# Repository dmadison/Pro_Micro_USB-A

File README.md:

Pro Micro w/ USB-A
=========

The Pro Micro is a micro controller with an ATMega32U4 IC on board.
The USB transceiver is inside the 32U4, adding USB connectivity on-board without external USB interfaces. 
This comes in both a 3.3V and 5V version. 

This repository was forked from [the original SparkFun Pro Micro repository](https://github.com/sparkfun/Pro_Micro). The board has been modified to use [a USB-A](https://en.wikipedia.org/wiki/USB_hardware#Connectors) connector.

For more information, see [the blog post on PartsNotIncluded.com](https://www.partsnotincluded.com/sparkfun-pro-micro-with-usb-a/).

Repository Contents
-------------------
* **/Documentation** - Data sheets (.pdf and .svg)
* **/Firmware** - Arduino example code used in the hookup guide
* **/Hardware** - All Eagle design files (.brd, .sch, .STL)
* **/Production** - Test bed files and production panel files

Documentation
--------------
* **[Hookup Guide](https://learn.sparkfun.com/tutorials/pro-micro--fio-v3-hookup-guide)** - Basic hookup guide for the Pro Micro.
* **[SparkFun Arduino Board Addon](https://github.com/sparkfun/Arduino_Boards/)** - Arduino board addon for Pro Micro.
* **[SparkFun Graphical Datasheets](https://github.com/sparkfun/Graphical_Datasheets)** - Graphical datasheets for various SparkFun products.
* **[USB-A Build Log](https://www.partsnotincluded.com/sparkfun-pro-micro-with-usb-a/)** - Build log for the USB-A version on PartsNotIncluded.com

Product Versions
----------------
* [DEV-12587](https://www.sparkfun.com/products/12587)- 3.3V/8MHz version
* [DEV-12640](https://www.sparkfun.com/products/12640)- 5V/16MHz version

License Information
-------------------
This product is _**open source**_! 

Please review the LICENSE.md file for license information. 

If you have any questions or concerns on licensing, please contact techsupport@sparkfun.com.

Distributed as-is; no warranty is given.

- Your friends at SparkFun.

_<COLLABORATION CREDIT>_

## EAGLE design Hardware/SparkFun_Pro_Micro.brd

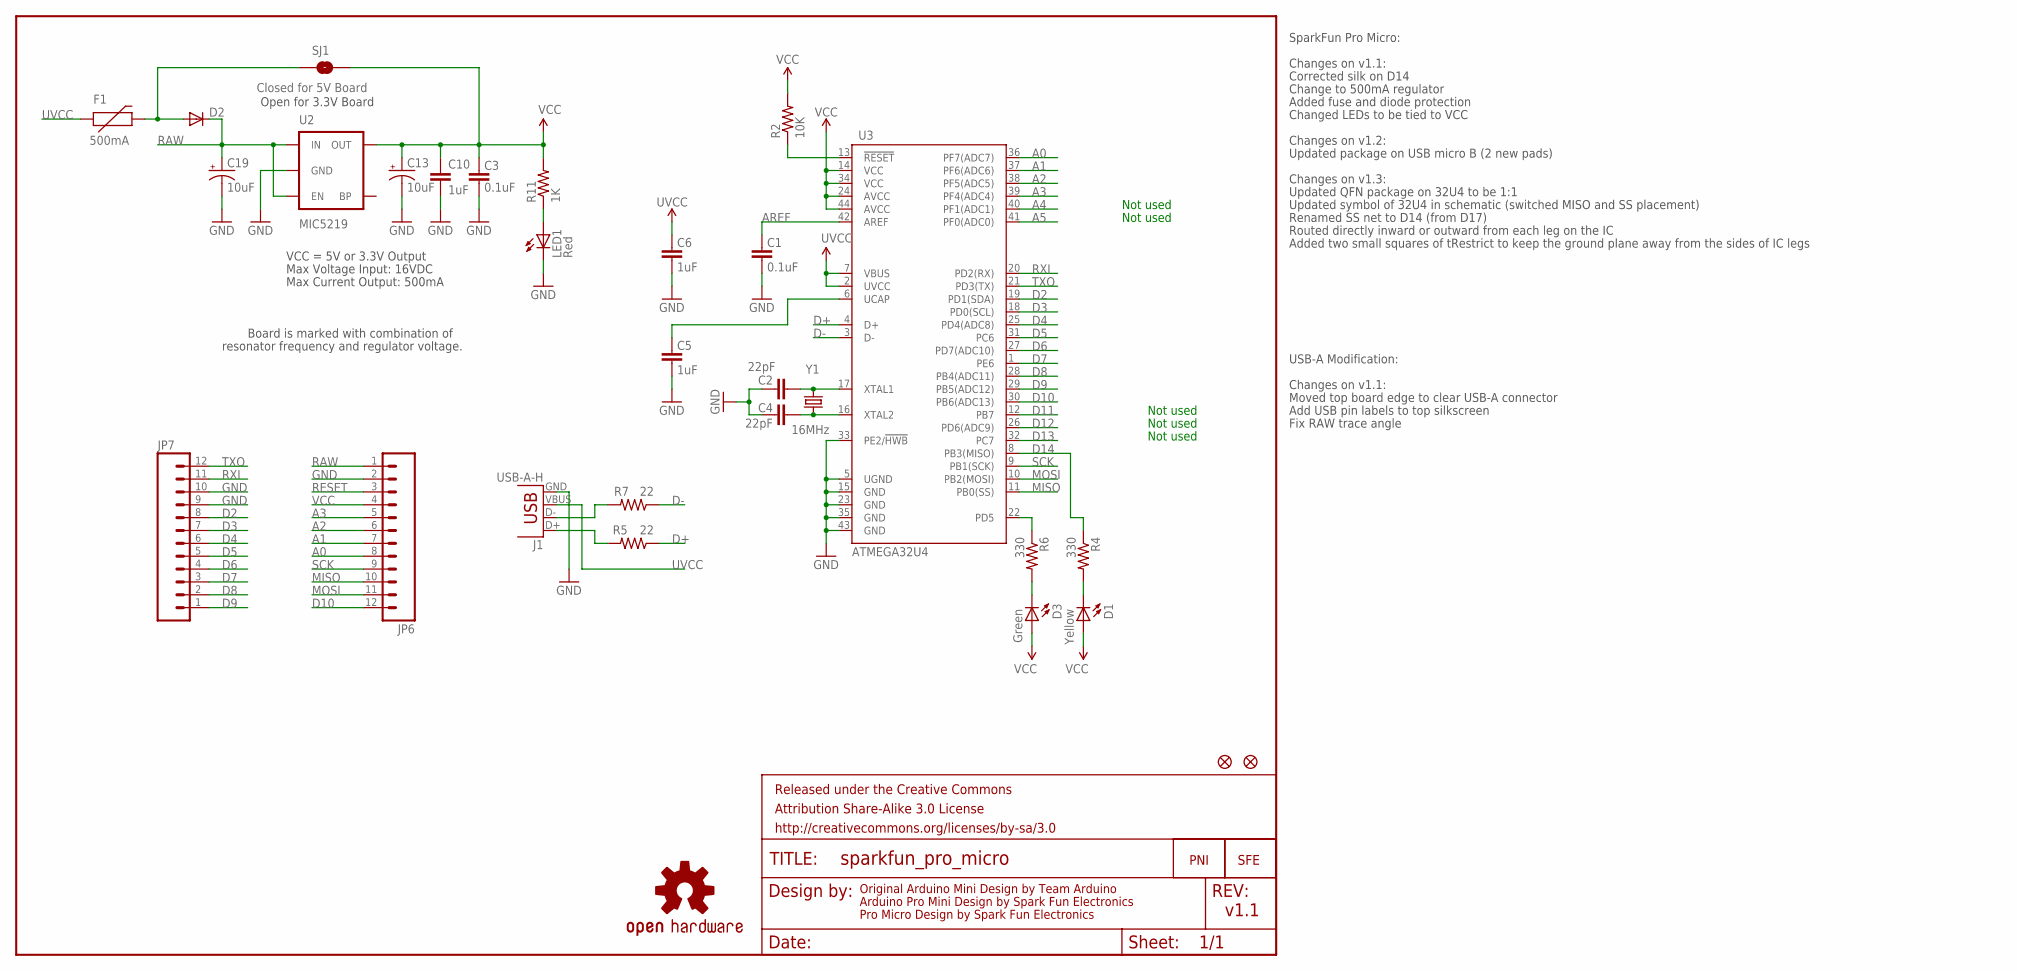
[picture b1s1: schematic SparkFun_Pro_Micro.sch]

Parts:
C1, C3: 0.1uF; 0603-CAP
C2, C4: 22pF; 0603-CAP
C5, C6, C10: 1uF; 0603-CAP
C13, C19: 10uF; EIA3216
D1: Yellow; LED-0603
D2: DIODESOD; SOD-323
D3: Green; LED-0603
F1: 500mA; PTC-1206
FRAME1: FRAME-LETTER; CREATIVE_COMMONS
J1: USB-A-H
JP1, JP2: FIDUCIALUFIDUCIAL; MICRO-FIDUCIAL
JP6, JP7: M12PTH; 1X12
LED1: Red; LED-0603
R2: 10K; 0603-RES
R4, R6: 330; 0603-RES
R5, R7: 22; 0603-RES
R11: 1K; 0603-RES
SJ1: Closed for 5V Board; SJ_2S
U2: MIC5219; SOT23-5
U3: ATMEGA32U4; QFN-44-NOPAD_1:1-OUTFAKES
U$1: LOGO-SFESK; SFE-LOGO-FLAME
U$2: PNI-PRO-MICRO-SPLIT-LOGO-TEXT
U$3: OSHW-LOGOS; OSHW-LOGO-S
Y1: 16MHz; CRYSTAL-SMD-5X3

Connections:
A0: JP6.8, U3.36 (PF7(ADC7))
A1: JP6.7, U3.37 (PF6(ADC6))
A2: JP6.6, U3.38 (PF5(ADC5))
A3: JP6.5, U3.39 (PF4(ADC4))
A4: U3.40 (PF1(ADC1))
A5: U3.41 (PF0(ADC0))
AREF: C1.2, U3.42 (AREF)
D2: JP7.8, U3.19 (PD1(SDA))
D3: JP7.7, U3.18 (PD0(SCL))
D4: JP7.6, U3.25 (PD4(ADC8))
D5: JP7.5, U3.31 (PC6)
D6: JP7.4, U3.27 (PD7(ADC10))
D7: JP7.3, U3.1 (PE6)
D8: JP7.2, U3.28 (PB4(ADC11))
D9: JP7.1, U3.29 (PB5(ADC12))
D10: JP6.12, U3.30 (PB6(ADC13))
D11: U3.12 (PB7)
D12: U3.26 (PD6(ADC9))
D13: U3.32 (PC7)
D14: R4.1, U3.8 (PB3(MISO))
D+: R5.1, U3.4 (D+)
D-: R7.1, U3.3 (D-)
GND: C1.1, C2.2, C3.1, C4.2, C5.1, C6.1, C10.2, C13.C (-), C19.C (-), J1.GND, JP6.2, JP7.9, JP7.10, LED1.C, U2.2 (GND), U3.5 (UGND), U3.15 (GND), U3.23 (GND), U3.33 (PE2/!HWB), U3.35 (GND), U3.43 (GND)
MISO: JP6.10, U3.11 (PB0(SS))
MOSI: JP6.11, U3.10 (PB2(MOSI))
unnamed: C4.1, U3.16 (XTAL2), Y1.1
unnamed: C2.1, U3.17 (XTAL1), Y1.3 (2)
unnamed: D2.2 (A), F1.2, SJ1.1
unnamed: C5.2, U3.6 (UCAP)
unnamed: D1.C, R4.2
unnamed: J1.D-, R7.2
unnamed: D3.C, R6.2
unnamed: J1.D+, R5.2
unnamed: LED1.A, R11.1
RAW: C19.A (+), D2.1 (C), JP6.1, U2.1 (IN), U2.3 (EN)
RESET: JP6.3, R2.1, U3.13 (!RESET)
RXI: JP7.11, U3.20 (PD2(RX))
SCK: JP6.9, U3.9 (PB1(SCK))
TXLED: R6.1, U3.22 (PD5)
TXO: JP7.12, U3.21 (PD3(TX))
UVCC: C6.2, F1.1, J1.VBUS, U3.2 (UVCC), U3.7 (VBUS)
VCC: C3.2, C10.1, C13.A (+), D1.A, D3.A, JP6.4, R2.2, R11.2, SJ1.2, U2.5 (OUT), U3.14 (VCC), U3.24 (AVCC), U3.34 (VCC), U3.44 (AVCC)

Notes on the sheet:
Original Arduino Mini Design by Team Arduino
Arduino Pro Mini Design by Spark Fun Electronics
Max Voltage Input: 16VDC
Max Current Output: 500mA
Board is marked with combination of
resonator frequency and regulator voltage.
VCC = 5V or 3.3V Output
Not used
Pro Micro Design by Spark Fun Electronics
Changes on v1.1:
Corrected silk on D14
Change to 500mA regulator
Open for 3.3V Board
Added fuse and diode protection
Changed LEDs to be tied to VCC
Changes on v1.2:
Updated package on USB micro B (2 new pads)
Changes on v1.3:
Updated QFN package on 32U4 to be 1:1
Updated symbol of 32U4 in schematic (switched MISO and SS placement)
Renamed SS net to D14 (from D17)
Routed directly inward or outward from each leg on the IC
Added two small squares of tRestrict to keep the ground plane away from the sides of IC legs
v1.1
SparkFun Pro Micro:
Moved top board edge to clear USB-A connector
Add USB pin labels to top silkscreen
Fix RAW trace angle
USB-A Modification:

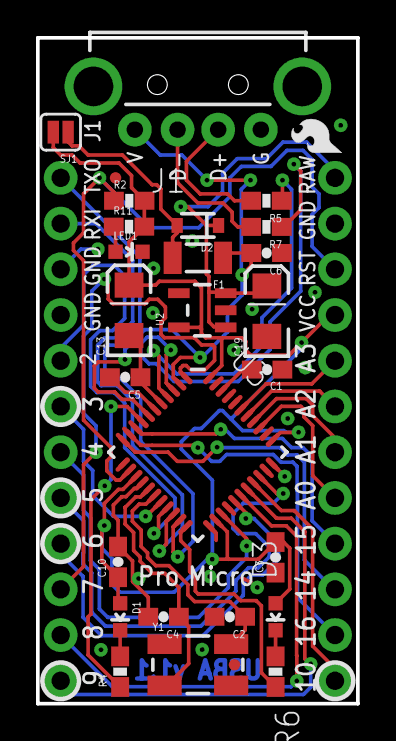
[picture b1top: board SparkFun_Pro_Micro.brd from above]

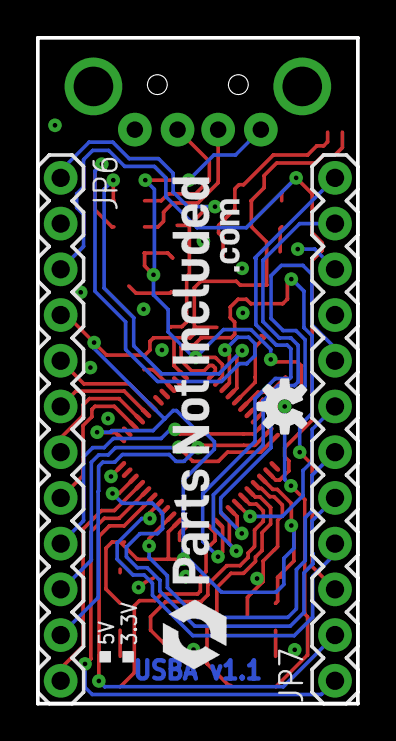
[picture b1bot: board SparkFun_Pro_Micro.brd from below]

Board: 2 copper layers, 17.8 x 37.0 mm, 33 parts (4 on the bottom side), 37 nets.

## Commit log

2020-02-23 Swap USB-B micro with USB-A male connector
2020-02-23 Add PartsNotIncluded logo to bottom silkscreen
2020-02-23 Remove SparkFun logo on bottom silkscreen
    This is cleverly hiding in the corner of the schematic as part of the title frame (look for "SFE" on the right).
2020-02-23 Update bottom copper version number for USBA
    "v1"!
2020-04-04 Move top board edge inwards to clear USB-A jack
    On version 1.0 the jack doesn't *quite* fit without a little sanding. It turns out that the footprint's silkscreen marker for the top of the board clearance area is off by 0.1 mm (3 mm in the footpri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
    Now according to the datasheet the lower edge of the connector is 18.8 mm from the tip, with the mounting tabs 2 mm long. Because the origin of the footprint is the center of these mounting tabs, tha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
2020-04-04 Add USB pin labels to top silkscreen
2020-04-04 Fix RAW trace angle
    This was not 45 degrees!
2020-04-04 Increase clearance around USB-A trace vias
2020-04-04 Tweak USB pin silkscreen labels to use "D" prefix
    More clearly distinguishing the data pins from the power and ground (which could also conceivably be confused with '+' and '-')
2020-04-04 USBA Version 1.1 on bottom copper
2020-04-06 Change README to USB-A
2020-04-06 Add README link to original SparkFun repository
2020-04-06 Add USB-A build log to README
2020-04-06 Update version number in schematic (v1.1)
    Using the USB-A version number instead of the Pro Micro number, for internal consistency
2020-04-06 Add USB-A version changes to schematic
2020-04-07 Center version number on bottom copper

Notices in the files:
parts and their libraries:
SparkFun-Aesthetics: Licensing: CC v3.0 Share-Alike You are welcome to use this library for commercial purposes.
SparkFun-Aesthetics: Released under the Creative Commons Attribution Share-Alike 3.0 License
SparkFun-Aesthetics: http://creativecommons.org/licenses/by-sa/3.0
